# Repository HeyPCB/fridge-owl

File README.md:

# Hoot, the fridge reminder owl

**The fridge owl that blinks at you until you've taken your meds and had your water.**

Hoot is a yellow owl-shaped fridge magnet with two reminders. Its left wing is a button marked "meds", its right wing "water". Press a wing when you have done the thing: that eye glows and its timer restarts. When the reminder comes due again (meds every 24 h or 12 h, water every 2 h), that orange LED eye blinks until you press. An ATtiny412 sleeps in power-down between one-second RTC ticks, so a CR2032 lasts about 14 months of typical use. Gold ENIG eye rings and beak on yellow mask; magnets go on the flat back.

| Layers | Size | Parts | Nets | Connections routed | Vias | ERC errors | DRC errors / unconnected / parity | BOM @100 |
|---|---|---|---|---|---|---|---|---|
| 2 | 42.1 x 53.3 mm | 10 (+3 pads) | 9 | 24 -> 0 open | 13 | 0 | 0 / 0 / 0 | $1.09 |

**Not fabricated, assembled or powered yet.** Every number on this page is measured by KiCad 10.0.6 on
the files in this repository ([`report.json`](report.json), [`measured.json`](measured.json)) or read
from the live JLC/LCSC catalogue ([`bom_cost.json`](bom_cost.json)).

| | |
|---|---|
| Spec, power budget, BOM | [`SPEC.md`](SPEC.md) |
| Store copy | [`STORE_COPY.md`](STORE_COPY.md) |
| KiCad 10 project | [`kicad/`](kicad/) |
| Gerbers, drill, BOM, CPL, STEP, schematic PDF | [`fab/`](fab/) |
| Firmware | [`firmware/`](firmware/) |
| Renders | [front](media/top.png), [back](media/bottom.png), [hero](media/hero.png), [Circuit World thumbnail](media/circuit-world.png) |
| Brief and generator | [`design/`](design/) |

## What's on it

- **Reminders:** meds (left wing, left eye) every 24 h, or 12 h by holding the wing 3 s; water (right wing, right eye) every 2 h.
- **Due:** that eye flashes every 2 s; after an hour unanswered it dozes to one flash every 10 s until a wing is pressed.
- **MCU:** ATtiny412 in power-down, woken once a second by the RTC and at once by a wing (PA2/PA6, the fully asynchronous pins); UPDI pads on the chin.
- **Power:** one CR2032 in a Keystone 3034 holder; about 17.5 µA on a typical day (see SPEC.md).
- **Mounting:** two 8 x 2 mm disc magnets on the rings printed on the back.

## Finish

Yellow solder mask, Black silkscreen, ENIG copper finish, 1.6 mm FR4, top-side SMT assembly.
The gold art is bare copper under a mask opening (ENIG), drawn with its own keep-out so no track runs
under it. The QR code on the back opens [https://heypcb.ai/world/b/01a4dcf69333](https://heypcb.ai/world/b/01a4dcf69333).

## How it was made

Designed with the HeyPCB method on KiCad 10.0.6, headless, by the `heypcb-kicad` pipeline: a written
brief composed from reusable circuit blocks, every pin from KiCad's own symbol library, every part bound
to an LCSC number from a dated catalogue read, then ERC, a netlist round trip, locked placement,
Freerouting 2.4.1, pours, silkscreen and board art, DRC with schematic parity, DFM and a fab gate,
each stage gated by a measurement. `design/make_brief.py` regenerates the brief (outline, part
locks and art) from code.

Part of the [heypcb.ai merch collection](https://github.com/HeyPCB/merch).

## License

Hardware: [CERN-OHL-S v2](LICENSE). Firmware: MIT (see [`firmware/LICENSE`](firmware/LICENSE)). KiCad's symbol, footprint and 3D
libraries used in the design are CC-BY-SA 4.0 with the KiCad library exception.

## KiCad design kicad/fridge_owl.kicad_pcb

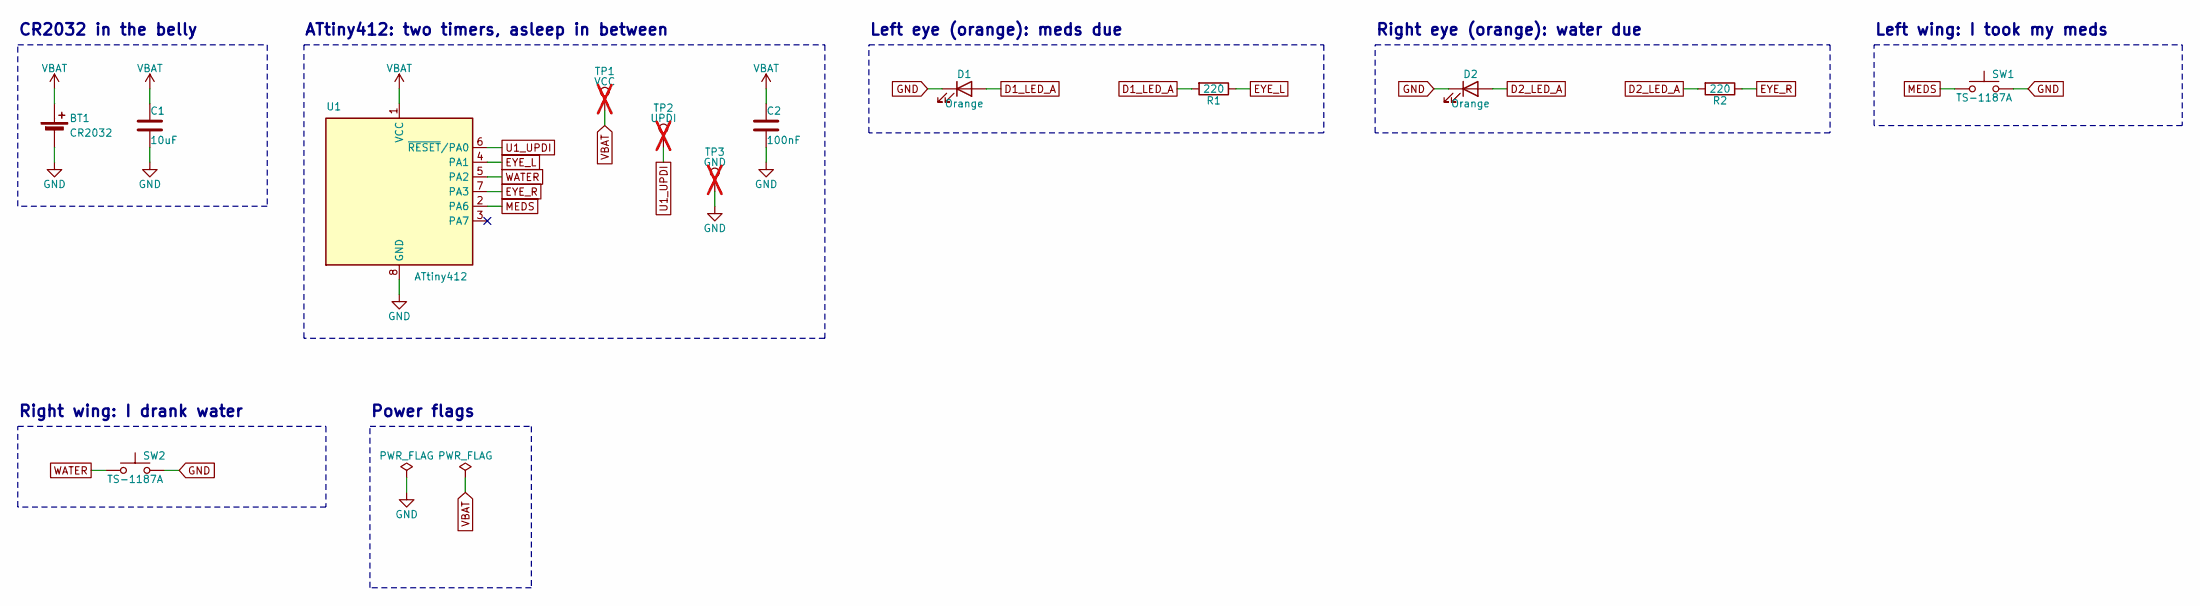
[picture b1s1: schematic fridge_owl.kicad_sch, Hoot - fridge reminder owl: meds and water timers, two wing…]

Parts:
BT1: CR2032; BatteryHolder_Keystone_3034_1x20mm; MPN 3034TR; LCSC C5213768
C1: 10uF; C_0805_2012Metric; MPN CL21A106KAYNNNE; LCSC C15850
C2: 100nF; C_0603_1608Metric; MPN CC0603KRX7R9BB104; LCSC C14663
D1, D2: Orange; LED_0603_1608Metric; MPN XL-1608UOC-06; LCSC C965800
R1, R2: 220; R_0603_1608Metric; MPN 0603WAF2200T5E; LCSC C22962
SW1, SW2: TS-1187A; SW_Push_1P1T_XKB_TS-1187A; MPN TS-1187A-B-A-B; LCSC C318884
TP1: VCC; TestPoint_Pad_1.0x1.0mm; not fitted
TP2: UPDI; TestPoint_Pad_1.0x1.0mm; not fitted
TP3: GND; TestPoint_Pad_1.0x1.0mm; not fitted
U1: ATtiny412; SOIC-8_3.9x4.9mm_P1.27mm; MPN ATTINY412-SSNR; LCSC C1337190

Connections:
D1_LED_A: D1.2 (A), R1.2
D2_LED_A: D2.2 (A), R2.2
EYE_L: R1.1, U1.4 (PA1)
EYE_R: R2.1, U1.7 (PA3)
GND: BT1.2 (-), C1.2, C2.2, D1.1 (K), D2.1 (K), SW1.2, SW2.2, TP3.1, U1.8 (GND)
MEDS: SW1.1, U1.2 (PA6)
U1_UPDI: TP2.1, U1.6 (~RESET/PA0)
VBAT: BT1.1 (+), C1.1, C2.1, TP1.1, U1.1 (VCC)
WATER: SW2.1, U1.5 (PA2)

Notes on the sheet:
CR2032 in the belly
ATtiny412: two timers, asleep in between
Left eye (orange): meds due
Right eye (orange): water due
Left wing: I took my meds
Right wing: I drank water
Power flags

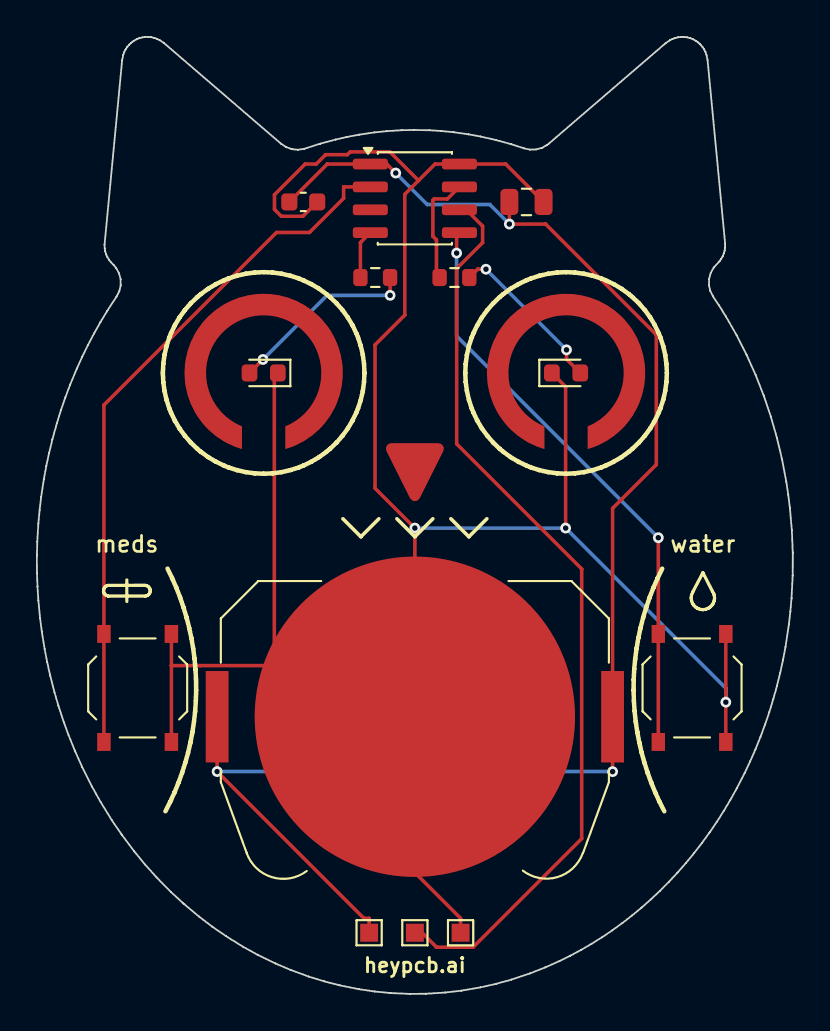
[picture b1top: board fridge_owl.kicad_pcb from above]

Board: 2 copper layers, 42.0 x 53.2 mm, 13 parts (0 on the bottom side), 9 nets.

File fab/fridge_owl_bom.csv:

"Reference","Value","Footprint","MPN","LCSC","Qty"
"BT1","CR2032","Battery:BatteryHolder_Keystone_3034_1x20mm","3034TR","C5213768","1"
"C1","10uF","Capacitor_SMD:C_0805_2012Metric","CL21A106KAYNNNE","C15850","1"
"C2","100nF","Capacitor_SMD:C_0603_1608Metric","CC0603KRX7R9BB104","C14663","1"
"D1,D2","Orange","LED_SMD:LED_0603_1608Metric","XL-1608UOC-06","C965800","2"
"R1,R2","220","Resistor_SMD:R_0603_1608Metric","0603WAF2200T5E","C22962","2"
"SW1,SW2","TS-1187A","Button_Switch_SMD:SW_Push_1P1T_XKB_TS-1187A","TS-1187A-B-A-B","C318884","2"
"U1","ATtiny412","Package_SO:SOIC-8_3.9x4.9mm_P1.27mm","ATTINY412-SSNR","C1337190","1"

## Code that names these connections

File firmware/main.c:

/*
 * Hoot, the fridge reminder owl - firmware for the ATtiny412 (heypcb.ai merch 08).
 *
 * What it does
 *   - Two reminders. The left wing is "meds" (every 24 h, or every 12 h), the right wing "water" (every
 *     2 h). Press a wing when you have done the thing: that eye glows "thank you" and its timer restarts.
 *   - When a reminder comes due, its eye blinks at you (a 30 ms flash every 2 s) until you press its wing.
 *     The left eye flashes on even seconds and the right on odd ones, so with both due the owl looks
 *     left and right.
 *   - An eye that has blinked for an hour unanswered dozes: one flash every 10 s, a fifth of the current,
 *     so a missed reminder is still there when you walk past (the night, a day out). Pressing either wing
 *     wakes it: somebody is home, so it blinks properly again.
 *   - Hold the meds wing 3 s to switch meds between 24 h and 12 h (the left eye answers with one slow
 *     flash for 24 h, two for 12 h). The choice is kept in EEPROM; the hold also counts as a press.
 *   - Putting the cell in: both eyes say hello and both reminders start due. Press each wing right after
 *     you next do the thing; that sets its time of day.
 *   - The rest of the time it sleeps in power-down. The RTC's periodic interrupt (1.024 kHz internal
 *     ultra-low-power oscillator) wakes it once a second to count; a wing press wakes it at once (PA2 and
 *     PA6 are the port's fully asynchronous pins, so a falling edge on them wakes power-down).
 *
 * Pins (from the board's netlist; KiCad symbol MCU_Microchip_ATtiny:ATtiny412-SS)
 *   PA1 (pin 4)  EYE_L  output, the left eye: orange LED through 220 ohm, high = on
 *   PA3 (pin 7)  EYE_R  output, the right eye
 *   PA6 (pin 2)  MEDS   input with pull-up, the left wing button to GND
 *   PA2 (pin 5)  WATER  input with pull-up, the right wing button to GND
 *   PA7 (pin 3)  not connected: pull-up on, so it never floats
 *   PA0 (pin 6)  UPDI   programming only
 *
 * Timekeeping: the internal oscillator is not a crystal, so the reminders run a few percent fast or
 * slow. Every press restarts its timer, so the error never adds up past one interval.
 *
 * Power budget (see SPEC.md for the arithmetic): about 17 uA on an average day, over a year on a CR2032.
 *
 * Build: make      (avr-gcc with ATtiny412 support; see README.md)
 */
#include <avr/eeprom.h>
#include <avr/interrupt.h>
#include <avr/io.h>
#include <avr/sleep.h>
#include <stdint.h>
#include <util/delay.h>

#define EYE_L PIN1_bm
#define WATER PIN2_bm
#define EYE_R PIN3_bm
#define MEDS PIN6_bm
#define SPARE PIN7_bm

#define HOUR 3600UL
#define NAG_S (1 * HOUR)      /* a due eye blinks every 2 s for an hour ... */
#define DOZE_EVERY_S 10u      /* ... then once every 10 s until somebody presses a wing */
#define FLASH_MS 30u
#define HOLD_MS 3000u

/* EEPROM: 1 = meds every 12 h; anything else (0xFF on a new chip) = every 24 h */
#define EE_MEDS_12H ((uint8_t *)0)

struct reminder {
    uint32_t every;     /* its interval, s */
    uint32_t left;      /* s until it is due; 0 = due */
    uint32_t nagged;    /* s it has blinked since it came due (or since a press woke it) */
    uint8_t eye;        /* its LED */
};

static struct reminder meds = {24 * HOUR, 0, 0, EYE_L};
static struct reminder water = {2 * HOUR, 0, 0, EYE_R};

static volatile uint8_t ticks;      /* seconds the RTC has counted that main() has not handled */
static volatile uint8_t pressed;    /* wings whose pin fell that main() has not handled */

ISR(RTC_PIT_vect)
{
    RTC.PITINTFLAGS = RTC_PI_bm;
    ticks++;
}

ISR(PORTA_PORT_vect)
{
    uint8_t f = PORTA.INTFLAGS;
    PORTA.INTFLAGS = f;
    pressed |= f & (MEDS | WATER);
}

static void count_second(struct reminder *r)
{
    if (r->left)
        r->left--;
    else if (r->nagged < NAG_S)
        r->nagged++;
}

/* Does this reminder's eye flash in second `s` (0..59)? Left eye on even seconds, right eye on odd. */
static uint8_t flashes(const struct reminder *r, uint8_t s)
{
    uint8_t odd = (r->eye == EYE_R);
    if (r->left)
        return 0;
    if (r->nagged < NAG_S)
        return (s & 1u) == odd;
    return s % DOZE_EVERY_S == (odd ? 5u : 0u);
}

static void flash(uint8_t pin, uint16_t ms)
{
    PORTA.OUTSET = pin;
    while (ms--)
        _delay_ms(1);
    PORTA.OUTCLR = pin;
}

/* A soft fade (software PWM at about 1 kHz): `steps_ms` steps of about 1 ms from one level to the other. */
static void glow(uint8_t pin, uint8_t from, uint8_t to, uint8_t steps_ms)
{
    for (uint8_t t = 0; t < steps_ms; t++) {
        uint8_t level = from + (int16_t)(to - from) * t / steps_ms;     /* 0..32 */
        for (uint8_t k = 0; k < 32; k++) {
            if (k < level)
                PORTA.OUTSET = pin;
            else
                PORTA.OUTCLR = pin;
            _delay_us(30);
        }
    }
    PORTA.OUTCLR = pin;
}

static void thanks(uint8_t eye)
{
    glow(eye, 0, 32, 120);
    glow(eye, 32, 0, 200);
}

static void restart(struct reminder *r)
{
    r->left = r->every;
    r->nagged = 0;
}

/* Somebody pressed a wing: an eye that dozed off over an unanswered reminder blinks properly again. */
static void wake(struct reminder *r)
{
    if (!r->left)
        r->nagged = 0;
}

static void set_meds(uint8_t twelve) { meds.every = (twelve ? 12u : 24u) * HOUR; }

static void on_press(uint8_t wing)
{
    _delay_ms(20);                          /* debounce */
    if (PORTA.IN & wing)
        return;                             /* a bounce, or the release of an earlier press */
    struct reminder *r = (wing == MEDS) ? &meds : &water;
    wake(&meds);
    wake(&water);
    thanks(r->eye);
    uint16_t held = 340;                    /* the debounce and the glow */
    while (!(PORTA.IN & wing) && held < HOLD_MS) {
        _delay_ms(10);
        held += 10;
    }
    if (wing == MEDS && held >= HOLD_MS) {
        uint8_t twelve = (meds.every != 12u * HOUR);                    /* switch it */
        eeprom_update_byte(EE_MEDS_12H, twelve);
        set_meds(twelve);
        for (uint8_t i = 0; i <= twelve; i++) {
            flash(EYE_L, 250);
            _delay_ms(250);
        }
        for (uint16_t t = 0; !(PORTA.IN & MEDS) && t < 1000; t++)
            _delay_ms(10);                  /* wait for the release (10 s at most) */
    }
    restart(r);
}

static void sleep_now(void)
{
    set_sleep_mode(SLEEP_MODE_PWR_DOWN);
    sleep_enable();
    sleep_cpu();
    sleep_disable();
}

int main(void)
{
    /* eyes off; the wings' pull-ups and wake-up edges; the unconnected pin pulled up */
    PORTA.DIRSET = EYE_L | EYE_R;
    PORTA.OUTCLR = EYE_L | EYE_R;
    PORTA.PIN6CTRL = PORT_PULLUPEN_bm | PORT_ISC_FALLING_gc;
    PORTA.PIN2CTRL = PORT_PULLUPEN_bm | PORT_ISC_FALLING_gc;
    PORTA.PIN7CTRL = PORT_PULLUPEN_bm;

    set_meds(eeprom_read_byte(EE_MEDS_12H) == 1);

    /* RTC periodic interrupt: 1.024 kHz internal ULP oscillator, 1024 cycles = 1 s */
    while (RTC.STATUS > 0)
        ;
    RTC.CLKSEL = RTC_CLKSEL_INT1K_gc;
    while (RTC.PITSTATUS > 0)
        ;
    RTC.PITINTCTRL = RTC_PI_bm;
    RTC.PITCTRLA = RTC_PERIOD_CYC1024_gc | RTC_PITEN_bm;
    sei();

    thanks(EYE_L);                          /* hello: left, then right */
    thanks(EYE_R);

    uint8_t s = 0;                          /* the second, 0..59, that picks which eye flashes */
    for (;;) {
        sleep_now();

        cli();
        uint8_t w = pressed;
        pressed = 0;
        uint8_t n = ticks;
        ticks = 0;
        sei();

        if (w & MEDS)
            on_press(MEDS);
        if (w & WATER)
            on_press(WATER);
        if (!n)
            continue;
        while (n--) {
            count_second(&meds);
            count_second(&water);
            s = (s + 1u) % 60u;
        }
        if (flashes(&meds, s))
            flash(EYE_L, FLASH_MS);
        if (flashes(&water, s))
            flash(EYE_R, FLASH_MS);
    }
}
